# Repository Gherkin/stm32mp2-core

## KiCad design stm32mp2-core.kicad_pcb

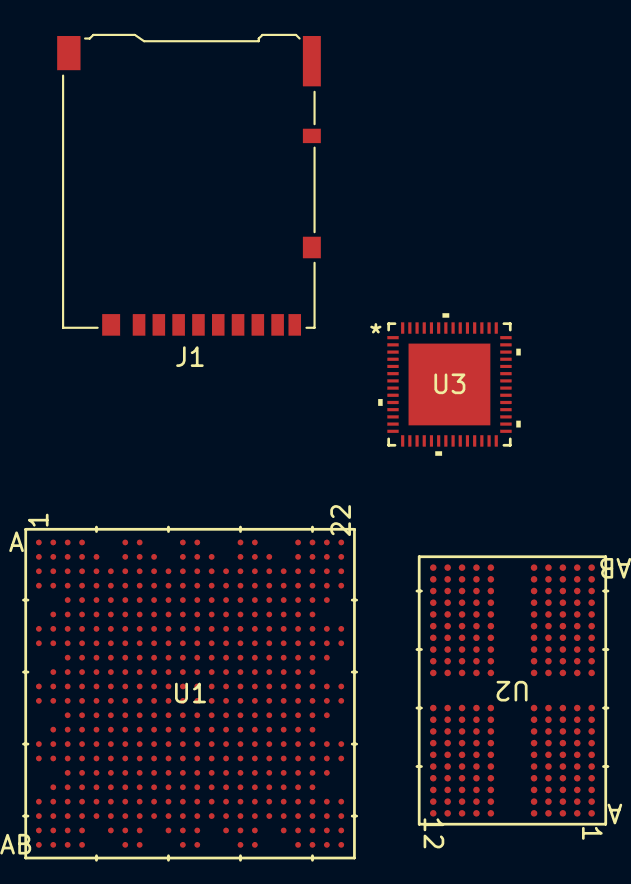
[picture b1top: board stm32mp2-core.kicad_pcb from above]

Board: 2 copper layers, 4 parts (0 on the bottom side), 69 nets, no tracks yet.

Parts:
J1: Micro_SD_Card_Det1; microSD_HC_Hirose_DM3AT-SF-PEJM5
U1: STM32MP257FAI3; TFBGA436_STM
U2: MT53E1G32D2FW-046 IT:B; VFBGA200_10X14.5X1.1FW_MRN-L
U3: STPMIC25APQR; WFQFN56L_6p5x6p5x0p9_STM-L

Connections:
+5V: U3.6 (LDO56IN), U3.11 (VIN), U3.15 (LDO12IN), U3.20 (BUCK4IN), U3.24 (BUCK3IN), U3.25 (BUCK2IN), U3.38 (BUCK5IN), U3.39 (BUCK1IN), U3.43 (LDO3IN), U3.49 (BUCK6IN), U3.50 (BUCK7IN)
/DDR.CAA2: U1.P19 (DDR_A8), U2.H9 (CA2_A)
/DDR.CAA3: U1.P18 (DDR_A9), U2.H10 (CA3_A)
/DDR.CAA4: U1.N18 (DDR_A10), U2.H11 (CA4_A)
/DDR.CAA5: U1.N17 (DDR_A11), U2.J11 (CA5_A)
/DDR.CAB0: U1.L18 (DDR_A14), U2.R2 (CA0_B)
/DDR.CAB1: U1.L17 (DDR_A15), U2.P2 (CA1_B)
/DDR.CAB2: U1.G18 (DDR_A20), U2.R9 (CA2_B)
/DDR.CAB3: U1.J19 (DDR_A21), U2.R10 (CA3_B)
/DDR.CAB4: U1.H17 (DDR_A22), U2.R11 (CA4_B)
/DDR.CAB5: U1.J17 (DDR_A23), U2.P11 (CA5_B)
/DDR.CLKA+: U1.N19 (DDR_A4), U2.J8 (CK_t_A)
/DDR.CLKA-: U1.M19 (DDR_A5), U2.J9 (CK_c_A)
/DDR.CLKB+: U1.J18 (DDR_A16), U2.P9 (CK_c_B)
/DDR.CLKB-: U1.H18 (DDR_A17), U2.P8 (CK_t_B)
/DDR.CSA0: U1.T18 (DDR_A6), U2.H4 (CS0_A)
/DDR.CSA1: U1.U19 (DDR_A7), U2.H3 (CS1_A)
/DDR.CSB0: U1.H19 (DDR_A18), U2.R4 (CS0_B)
/DDR.CSB1: U1.K17 (DDR_A19), U2.R3 (CS1_B)
/DDR.DMIA0: U1.W21 (DDR_DQM0), U2.C3 (DMI0_A)
/DDR.DMIA1: U1.P20 (DDR_DQM1), U2.C10 (DMI1_A)
/DDR.DMIB0: U1.E21 (DDR_DQM2), U2.Y3 (DMI0_B)
/DDR.DMIB1: U1.H20 (DDR_DQM3), U2.Y10 (DMI1_B)
/DDR.DQ0_0: U1.W22 (DDR_DQ0), U2.B2 (DQ0_A)
/DDR.DQ0_1: U1.Y21 (DDR_DQ1), U2.C2 (DQ1_A)
/DDR.DQ0_2: U1.Y22 (DDR_DQ2), U2.E2 (DQ2_A)
/DDR.DQ0_3: U1.AA22 (DDR_DQ3), U2.F2 (DQ3_A)
/DDR.DQ0_4: U1.T21 (DDR_DQ4), U2.F4 (DQ4_A)
/DDR.DQ0_5: U1.T20 (DDR_DQ5), U2.E4 (DQ5_A)
/DDR.DQ0_6: U1.U21 (DDR_DQ6), U2.C4 (DQ6_A)
/DDR.DQ0_7: U1.U20 (DDR_DQ7), U2.B4 (DQ7_A)
/DDR.DQ1_0: U1.M21 (DDR_DQ8), U2.B11 (DQ8_A)
/DDR.DQ1_1: U1.M22 (DDR_DQ9), U2.C11 (DQ9_A)
/DDR.DQ1_2: U1.L21 (DDR_DQ10), U2.E11 (DQ10_A)
/DDR.DQ1_3: U1.L22 (DDR_DQ11), U2.F11 (DQ11_A)
/DDR.DQ1_4: U1.T22 (DDR_DQ12), U2.F9 (DQ12_A)
/DDR.DQ1_5: U1.R20 (DDR_DQ13), U2.E9 (DQ13_A)
/DDR.DQ1_6: U1.R21 (DDR_DQ14), U2.C9 (DQ14_A)
/DDR.DQ1_7: U1.R22 (DDR_DQ15), U2.B9 (DQ15_A)
/DDR.DQ2_0: U1.D20 (DDR_DQ16), U2.AA2 (DQ0_B)
/DDR.DQ2_1: U1.C22 (DDR_DQ17), U2.Y2 (DQ1_B)
/DDR.DQ2_2: U1.C21 (DDR_DQ18), U2.V2 (DQ2_B)
/DDR.DQ2_3: U1.B22 (DDR_DQ19), U2.U2 (DQ3_B)
/DDR.DQ2_4: U1.F20 (DDR_DQ20), U2.U4 (DQ4_B)
/DDR.DQ2_5: U1.F19 (DDR_DQ21), U2.V4 (DQ5_B)
/DDR.DQ2_6: U1.E19 (DDR_DQ22), U2.Y4 (DQ6_B)
/DDR.DQ2_7: U1.E20 (DDR_DQ23), U2.AA4 (DQ7_B)
/DDR.DQ3_0: U1.G19 (DDR_DQ24), U2.AA11 (DQ8_B)
/DDR.DQ3_1: U1.G22 (DDR_DQ25), U2.Y11 (DQ9_B)
/DDR.DQ3_2: U1.G21 (DDR_DQ26), U2.V11 (DQ10_B)
/DDR.DQ3_3: U1.G20 (DDR_DQ27), U2.U11 (DQ11_B)
/DDR.DQ3_4: U1.J21 (DDR_DQ28), U2.U9 (DQ12_B)
/DDR.DQ3_5: U1.J20 (DDR_DQ29), U2.V9 (DQ13_B)
/DDR.DQ3_6: U1.K20 (DDR_DQ30), U2.Y9 (DQ14_B)
/DDR.DQ3_7: U1.L19 (DDR_DQ31), U2.AA9 (DQ15_B)
/DDR.DQS0+: U1.V20 (DDR_DQS0P), U2.D3 (DQS0_t_A)
/DDR.DQS0-: U1.W20 (DDR_DQS0N), U2.E3 (DQS0_c_A)
/DDR.DQS1+: U1.N20 (DDR_DQS1P), U2.D10 (DQS1_t_A)
/DDR.DQS1-: U1.N21 (DDR_DQS1N), U2.E10 (DQS1_c_A)
/DDR.DQS2+: U1.D21 (DDR_DQS2P), U2.W3 (DQS0_t_B)
/DDR.DQS2-: U1.D22 (DDR_DQS2N), U2.V3 (DQS0_c_B)
/DDR.DQS3+: U1.H22 (DDR_DQS3P), U2.W10 (DQS1_t_B)
/DDR.DQS3-: U1.H21 (DDR_DQS3N), U2.V10 (DQS1_c_B)
/DDR.RESET#: U1.F18 (DDR_RESETN), U2.T11 (RESET_n)
/STM32MP25/STM32MP25_PAGE_2/LVDS1.D0-: U1.B4 (LVDS2_D0N), U1.D3 (LVDS1_D0N)
GND: J1.6 (VSS), J1.10 (SHIELD), U2.A3 (VSS), U2.A10 (VSS), U2.AB3 (VSS), U2.AB5 (VSS), U2.AB8 (VSS), U2.AB10 (VSS), U2.C1 (VSS), U2.C5 (VSS), U2.C8 (VSS), U2.C12 (VSS), U2.D2 (VSS), U2.D4 (VSS), U2.D9 (VSS), U2.D11 (VSS), U2.E1 (VSS), U2.E5 (VSS), U2.E8 (VSS), U2.E12 (VSS), U2.G1 (VSS), U2.G3 (VSS), U2.G5 (VSS), U2.G8 (VSS), U2.G10 (VSS), U2.G12 (VSS), U2.J1 (VSS), U2.J3 (VSS), U2.J10 (VSS), U2.J12 (VSS), U2.K2 (VSS), U2.K4 (VSS), U2.K9 (VSS), U2.K11 (VSS), U2.N2 (VSS), U2.N4 (VSS), U2.N9 (VSS), U2.N11 (VSS), U2.P1 (VSS), U2.P3 (VSS), U2.P10 (VSS), U2.P12 (VSS), U2.T1 (VSS), U2.T3 (VSS), U2.T5 (VSS), U2.T8 (VSS), U2.T10 (VSS), U2.T12 (VSS), U2.V1 (VSS), U2.V5 (VSS), U2.V8 (VSS), U2.V12 (VSS), U2.W2 (VSS), U2.W4 (VSS), U2.W9 (VSS), U2.W11 (VSS), U2.Y1 (VSS), U2.Y5 (VSS), U2.Y8 (VSS), U2.Y12 (VSS)
VDD1: U2.F1 (VDD1), U2.F12 (VDD1), U2.G4 (VDD1), U2.G9 (VDD1), U2.T4 (VDD1), U2.T9 (VDD1), U2.U1 (VDD1), U2.U12 (VDD1)
VDD2: U2.A4 (VDD2), U2.A9 (VDD2), U2.AB4 (VDD2), U2.AB9 (VDD2), U2.F5 (VDD2), U2.F8 (VDD2), U2.H1 (VDD2), U2.H5 (VDD2), U2.H8 (VDD2), U2.H12 (VDD2), U2.K1 (VDD2), U2.K3 (VDD2), U2.K10 (VDD2), U2.K12 (VDD2), U2.N1 (VDD2), U2.N3 (VDD2), U2.N10 (VDD2), U2.N12 (VDD2), U2.R1 (VDD2), U2.R5 (VDD2), U2.R8 (VDD2), U2.R12 (VDD2), U2.U5 (VDD2), U2.U8 (VDD2)
VDDQ: U2.AA3 (VDDQ), U2.AA5 (VDDQ), U2.AA8 (VDDQ), U2.AA10 (VDDQ), U2.B3 (VDDQ), U2.B5 (VDDQ), U2.B8 (VDDQ), U2.B10 (VDDQ), U2.D1 (VDDQ), U2.D5 (VDDQ), U2.D8 (VDDQ), U2.D12 (VDDQ), U2.F3 (VDDQ), U2.F10 (VDDQ), U2.U3 (VDDQ), U2.U10 (VDDQ), U2.W1 (VDDQ), U2.W5 (VDDQ), U2.W8 (VDDQ), U2.W12 (VDDQ)

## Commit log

2025-03-25 init
2025-03-25 did more stuff
2025-03-26 did stuff
2025-09-14 started on lpddr4
2025-09-14 connected lpddr4 to mp
2025-09-15 got started on the pmic
2025-09-15 added sd card holder for fun
2025-09-17 added the missing pins from the stupid pmic ultralibrarian symbol
2025-09-18 more pmic work
